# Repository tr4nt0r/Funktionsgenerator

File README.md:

# Funktionsgenerator
Funktionsgenerator basierend auf dem DDS AD9833 mit einem Atmega328PB (Arduino) als Mikrocontroller und einem 1,8" TFT Display

Function generator with AD9833 DDS, Atmega328PB Microcontroller and a 1.8" TFT Display

## Bill of Materials
### AD9833 & µController Board

| Qty | Value | Device | Package | Description | Vendor | Price |
| ---: | :--- | :--- | :--- | :--- | :--- | ---: |
| 1 | | KMR-1.8 SPI ST7735R | | 1.8" TFT Display |  [eBay](https://www.ebay.de/sch/i.html?_from=R40&_trksid=m570.l1313&_nkw=1%2C8%22+tft+spi+st7735r&_sacat=0) | 2,88€ |
| 1 | | SPDT | | Toggle switch for Front Panel Mount | [eBay](https://www.ebay.de/sch/i.html?_from=R40&_trksid=p2380057.m570.l1313.TR12.TRC2.A0.H0.Xtoggle+switch+12mm.TRS0&_nkw=toggle+switch+12mm&_sacat=0) | 3,00€ |
| 1 |  | KY-040 | | Rotary Encoder mit Taster (Ausführung mit Gewinde am Schaft und Befestigungsmutter) |  [eBay](https://www.ebay.de/itm/Drehregler-Drehgeber-Rotary-Encoder-Arduino-KY-040-Potentiometer-Poti-Raspberry/252713917550?hash=item3ad6ec5c6e:g:pIYAAOSwn25aD28N)| 4€ |
| 1 | 1,3k | Resistor | 0603 | | | 0,01€
| 1 | 620 | Resistor | 0603 |||0,01€|
| 8 | 100n | Capacitor | 0603 | | | 0,01€
| 4 | 10k | Resistor | 0603 ||| 0,01€|
| 1 | 10n | Capacitor| 0603||| 0,01€ |
| 1 |16Mhz | Crystal | SMD HC-49/U-S | 16.000MHz QCS HC49/U-S SMD Crystal 16MHz, 20ppm, 2-Pin HC-49/U-S SMD | [RS Components](https://de.rs-online.com/web/p/quarzmodule/8149535/)|0,25€|
| 1 | 1k |Potentiometer|| for Front Panel Mount | [RS Components](https://de.rs-online.com/web/p/products/8427030/)| 5,88€|
| 1 | 25k | Potentiometer || for Front Panel Mount| [RS Components](https://de.rs-online.com/web/p/products/8427059/)| 5,85€|
| 2 | 22p | Capacitor | 0603 | || 0,01€|
| 1 | 24.0Mhz | CFPS-72 | 7 x 5 mm SMD | | [RS Components](https://de.rs-online.com/web/p/products/8141581/)|1,25€|
|1 | 330n | Capacitor | 0603 | || 0,01€|
| 1 | | AD9833BRMZ | MSOP-10 | Programmable Waveform Generator | [Mouser](https://www.mouser.de/ProductDetail/Analog-Devices/AD9833BRMZ?qs=BpaRKvA4VqFt3Bdw9RBKCQ%3D%3D&gclid=Cj0KCQjwjtLZBRDLARIsAKT6fXx8JGdQ5f7k4kLWN22pvajQKU_Hv3pxUgl8WFMx-up7iK0Du9SND08aAm8KEALw_wcB) or [eBay](https://www.ebay.de/sch/i.html?_osacat=0&_odkw=AD9833BRMZ&_from=R40&_trksid=m570.l1313&_nkw=AD9833BRMZ+msop&_sacat=0)|7,79€|
| 1 | | ATMEGA328PB-AU | TQFP-32 | ATMEL - ATMEGA328PB-AU - MCU, 8BIT, ATMEGA, 20MHZ | [RS Components](https://de.rs-online.com/web/p/products/1468920/)|1,61€|
| 1 | 50Ohm | BNC Connector | | for Front Panel Mount | [RS Components](https://de.rs-online.com/web/p/products/5121174/)|2,15€|
| 1 | 10u | EEEFK1C100AR | Panasonic B | Panasonic 10uF 16 Vdc SMD Electrolytic Capacitor | [RS Components](https://de.rs-online.com/web/p/products/0565572/)|0,45€|
| 1 | 47u | Capacitor | Case D| Polarized Tantal Capacitor 10Vdc | [RS Components](https://de.rs-online.com/web/p/products/6993175/) | 0,36€|
| 2 | | LM318D | SO-08 | OpAmp | [RS Components](https://de.rs-online.com/web/p/products/6610524/) | 1,64€|
| 1 | | TLE4270-2D | TO-252 | LDO Voltage Regulator, 850mA, 5 V | [RS Components](https://de.rs-online.com/web/p/ldo-spannungsregler/1109087/) | 2,44€|

### Power Supply Board

| Qty | Value | Device | Package | Description | Vendor | Price |
| ---: | :--- | :--- | :--- | :--- | :--- | ---: |
|2 | 100n| Capacitor | 0603 | ||| 0,01€|
|1 | 2x12V 6VA | Transformer | | PCB Mount | [RS Components](https://de.rs-online.com/web/p/products/1213841/) | 5,75€|
|2 | 100u | EEEFT1C101AR | Panasonic C | Panasonic 100uF 16 Vdc SMD Electrolytic Capacitor | [RS Components](https://de.rs-online.com/web/p/aluminium-elektrolytkondensatoren/7472499/) | 0,35€|
|2 | 1000u/35V | Electrolyic Capacitor |E5-13| | [RS Components](https://de.rs-online.com/web/p/aluminium-elektrolytkondensatoren/7111337/) | 0,46€|
|1 | | MB6S| SOIC-4 | Bridge Rectifier | [RS Components](https://de.rs-online.com/web/p/products/6290322/)|0,35€|
| 1 |+12V| MC7812|DPAK| Positive Voltage Regulator| [RS Components](https://de.rs-online.com/web/p/products/6889250/)|0,70€|
|1|-12V| MC79M12|DPAK | Netgative Voltage Regulator|[RS Components](https://de.rs-online.com/web/p/products/6889326/)|0,65€|

#### Pin Connectors
You will need several pin headers and connectors , 2x2 Pin, 2x3 Pin, 1x 5 Pin. You could use any connector with a pitch of 0,1"/2,54mm either regular pinheaders or [Molex KK 254 Connectors](https://de.rs-online.com/web/c/steckverbinder/leiterplattensteckverbinder/leiterplatten-header/?redirect-relevancy-data=636F3D3126696E3D4931384E53656172636847656E65726963266C753D6465266D6D3D6D61746368616C6C7061727469616C26706D3D5E2E2A2426706F3D31333326736E3D592673723D52656469726563742673743D43415443485F414C4C5F44454641554C542673633D592677633D4E4F4E45267573743D73746966746C6569737465267374613D73746966746C656973746526&r=f&applied-dimensions=4294965668,4293240458,4294519411,4294519436,4294516238,4294878123).

### Images

This work is based on this [howto](https://www.allaboutcircuits.com/projects/how-to-DIY-waveform-generator-analog-devices-ad9833-ATmega328p/) from allaboutcircuits.com

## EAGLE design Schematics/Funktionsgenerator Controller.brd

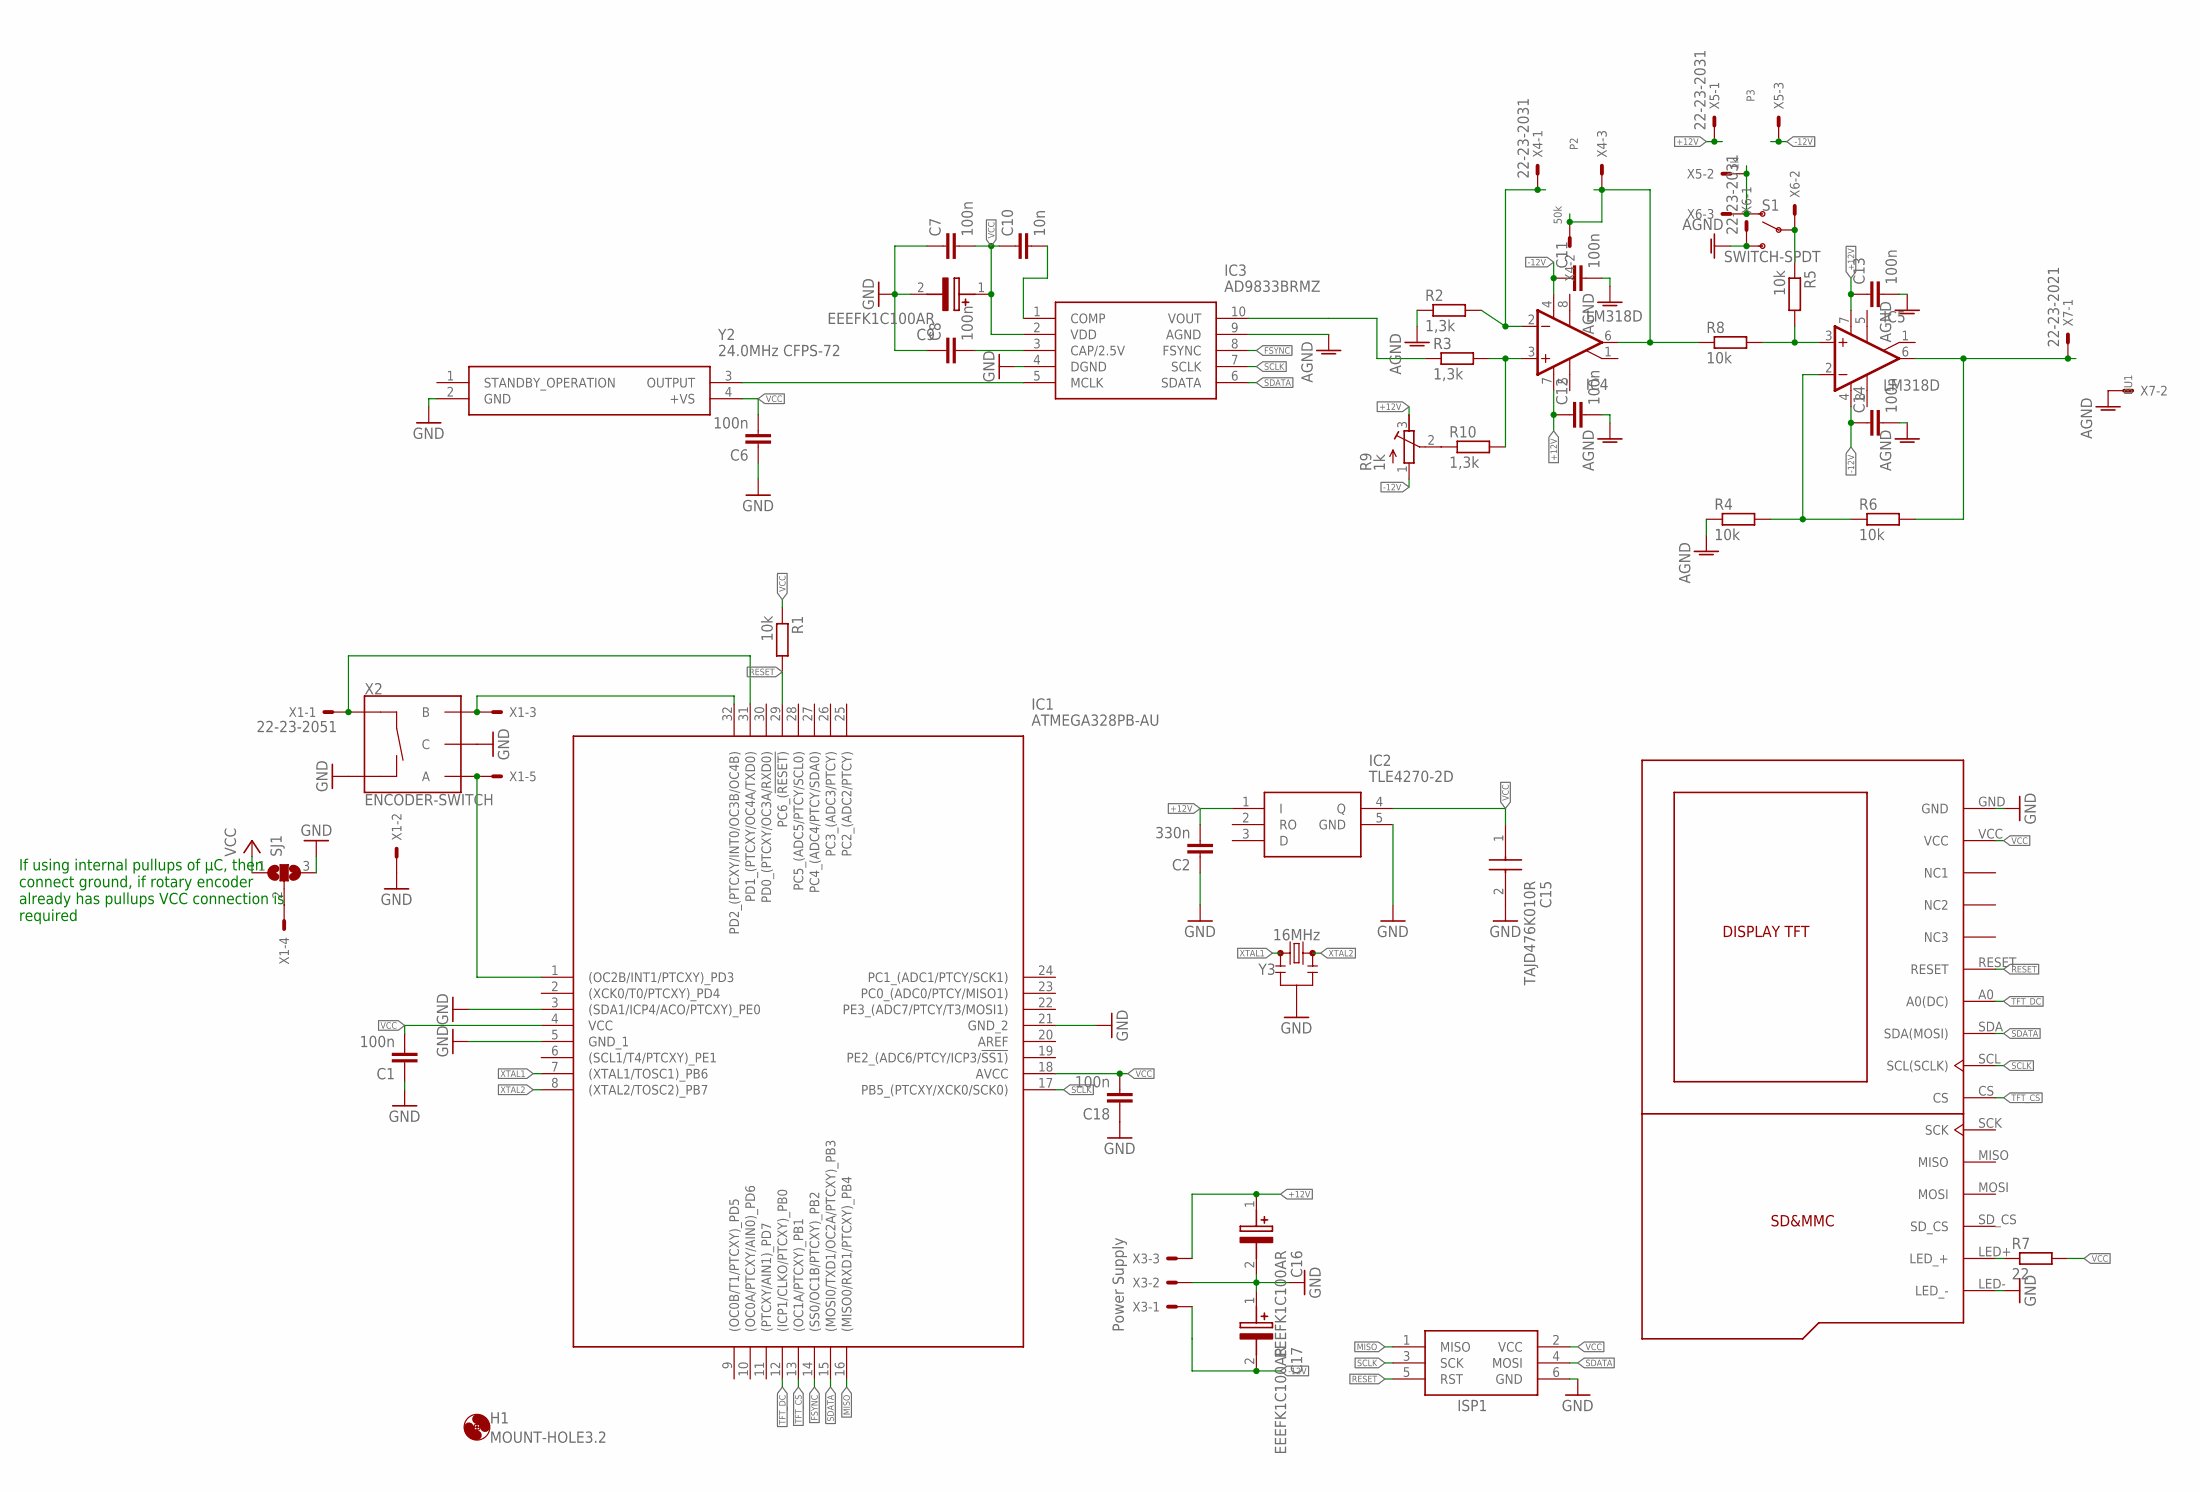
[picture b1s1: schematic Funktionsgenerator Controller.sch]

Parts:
C1, C6, C7, C8, C11, C12, C13, C14, C18: 100n; C0603
C2: 330n; C0603
C9, C16, C17: EEEFK1C100AR; FKV(B)
C10: 10n; C0603
C15: TAJD476K010R; CAPPM7344X310N
H1: MOUNT-HOLE3.2; 3,2
IC1: ATMEGA328PB-AU; QFP80P900X900X120-32N
IC2: TLE4270-2D; PG-TO252-5-11
IC3: AD9833BRMZ; SOP50P490X110-10N
IC4, IC5: LM318D; SO08
ISP1: AVRISP-6; AVRISP
P1: DISPLAY_TFT_1,8; DISPLAY_TFT_1,8-KMR
R1, R4, R5, R6, R8: 10k; R0603
R2, R3, R10: 1,3k; R0603
R7: 22; R0603
R9: 1k; EVM3ESX50B
SJ1: SJ2W; SJ_2
X1: 22-23-2051
X3: Power Supply; 22-23-2031
X4, X5, X6: 22-23-2031
X7: 22-23-2021
Y2: 24.0MHz CFPS-72; CFPS-72
Y3: 16MHz; RESONATOR-SMD-3.2X1.3

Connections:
+12V: C2.2, C12.1, C13.1, C16.1 (+), IC2.1 (I), IC4.7 (V+), IC5.7 (V+), R9.3 (E), X3.3, X5.1
-12V: C11.1, C14.1, C17.2 (-), IC4.4 (V-), IC5.4 (V-), R9.1 (A), X3.1, X5.3
AGND: C11.2, C12.2, C13.2, C14.2, IC3.9 (AGND), R2.1, R4.1, X6.1, X7.2
FSYNC: IC1.14 ((SS0/OC1B/PTCXY)_PB2), IC3.8 (FSYNC)
GND: C1.1, C2.1, C6.1, C7.1, C8.1, C9.2 (-), C15.2 (-), C16.2 (-), C17.1 (+), C18.1, IC1.3 ((SDA1/ICP4/ACO/PTCXY)_PE0), IC1.5 (GND_1), IC1.21 (GND_2), IC2.5 (GND), IC3.4 (DGND), ISP1.6 (GND), P1.GND, P1.LED- (LED_-), SJ1.3, X1.2, X3.2, Y2.2 (GND), Y3.2
MISO: IC1.16 ((MISO0/RXD1/PTCXY)_PB4), ISP1.1 (MISO)
unnamed: IC3.5 (MCLK), Y2.3 (OUTPUT)
unnamed: C8.2, IC3.3 (CAP/2.5V)
unnamed: IC4.3 (+IN), R3.2, R10.2
unnamed: C10.2, IC3.1 (COMP)
unnamed: IC3.10 (VOUT), R3.1
unnamed: IC4.2 (-IN), R2.2, X4.1
unnamed: R5.1, X6.2
unnamed: X5.2, X6.3
unnamed: IC4.6 (OUT), R8.1, X4.2, X4.3
unnamed: IC5.6 (OUT), R6.2, X7.1
unnamed: IC5.2 (-IN), R4.2, R6.1
unnamed: SJ1.2, X1.4
unnamed: IC5.3 (+IN), R5.2, R8.2
unnamed: R9.2 (S), R10.1
unnamed: P1.LED+ (LED_+), R7.1
RESET: IC1.29 (PC6_(!RESET)), ISP1.5 (RST), P1.RESET, R1.2
ROT_A: IC1.1 ((OC2B/INT1/PTCXY)_PD3), X1.5
ROT_B: IC1.32 (PD2_(PTCXY/INT0/OC3B/OC4B)), X1.3
ROT_BTN: IC1.31 (PD1_(PTCXY/OC4A/TXD0)), X1.1
SCLK: IC1.17 (PB5_(PTCXY/XCK0/SCK0)), IC3.7 (SCLK), ISP1.3 (SCK), P1.SCL (SCL(SCLK))
SDATA: IC1.15 ((MOSI0/TXD1/OC2A/PTCXY)_PB3), IC3.6 (SDATA), ISP1.4 (MOSI), P1.SDA (SDA(MOSI))
TFT_CS: IC1.13 ((OC1A/PTCXY)_PB1), P1.CS
TFT_DC: IC1.12 ((ICP1/CLKO/PTCXY)_PB0), P1.A0 (A0(DC))
VCC: C1.2, C6.2, C7.2, C9.1 (+), C10.1, C15.1 (+), C18.2, IC1.4 (VCC), IC1.18 (AVCC), IC2.4 (Q), IC3.2 (VDD), ISP1.2 (VCC), P1.VCC, R1.1, R7.2, SJ1.1, Y2.4 (+VS)
XTAL1: IC1.7 ((XTAL1/TOSC1)_PB6), Y3.1
XTAL2: IC1.8 ((XTAL2/TOSC2)_PB7), Y3.3

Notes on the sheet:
If using internal pullups of µC, then connect ground, if rotary encoder already has pullups VCC connection is required

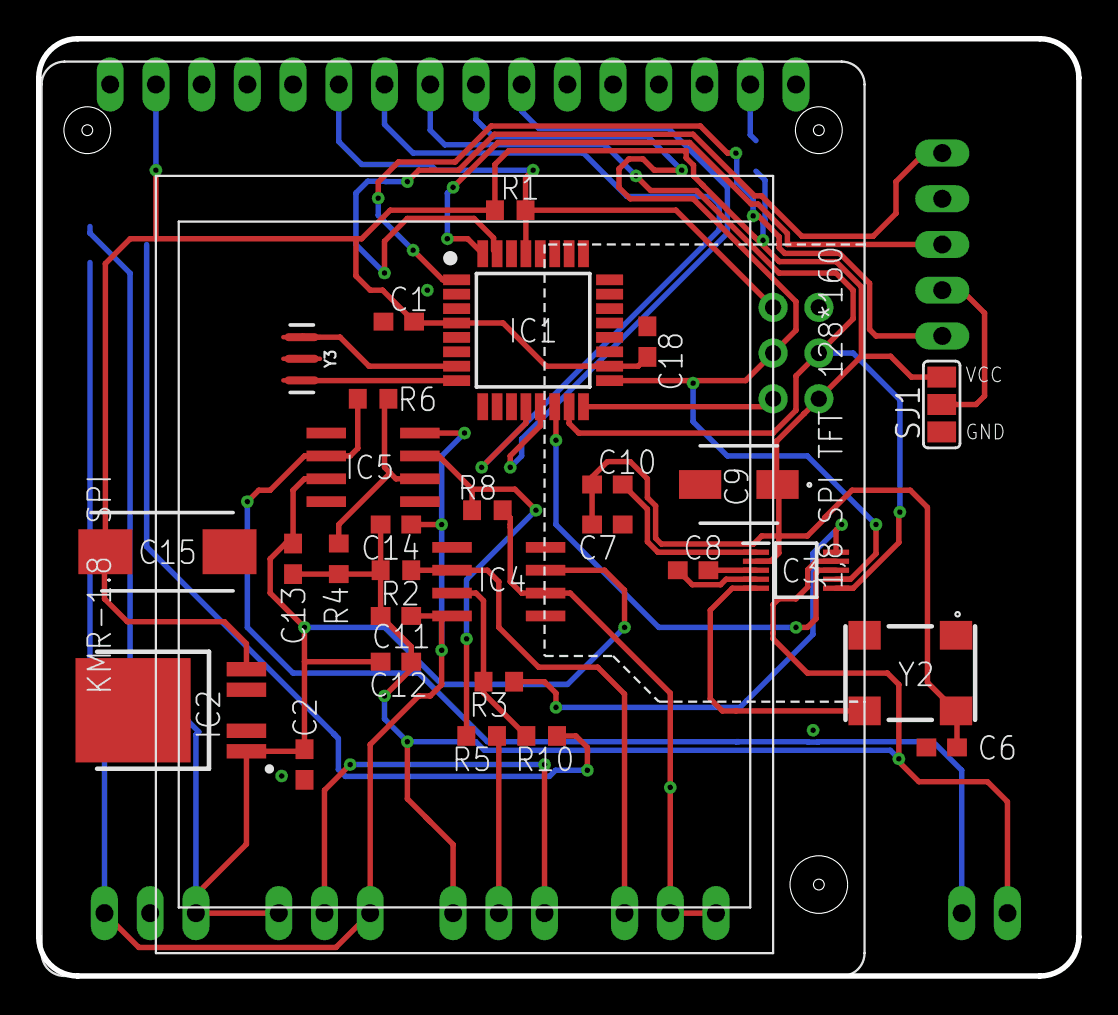
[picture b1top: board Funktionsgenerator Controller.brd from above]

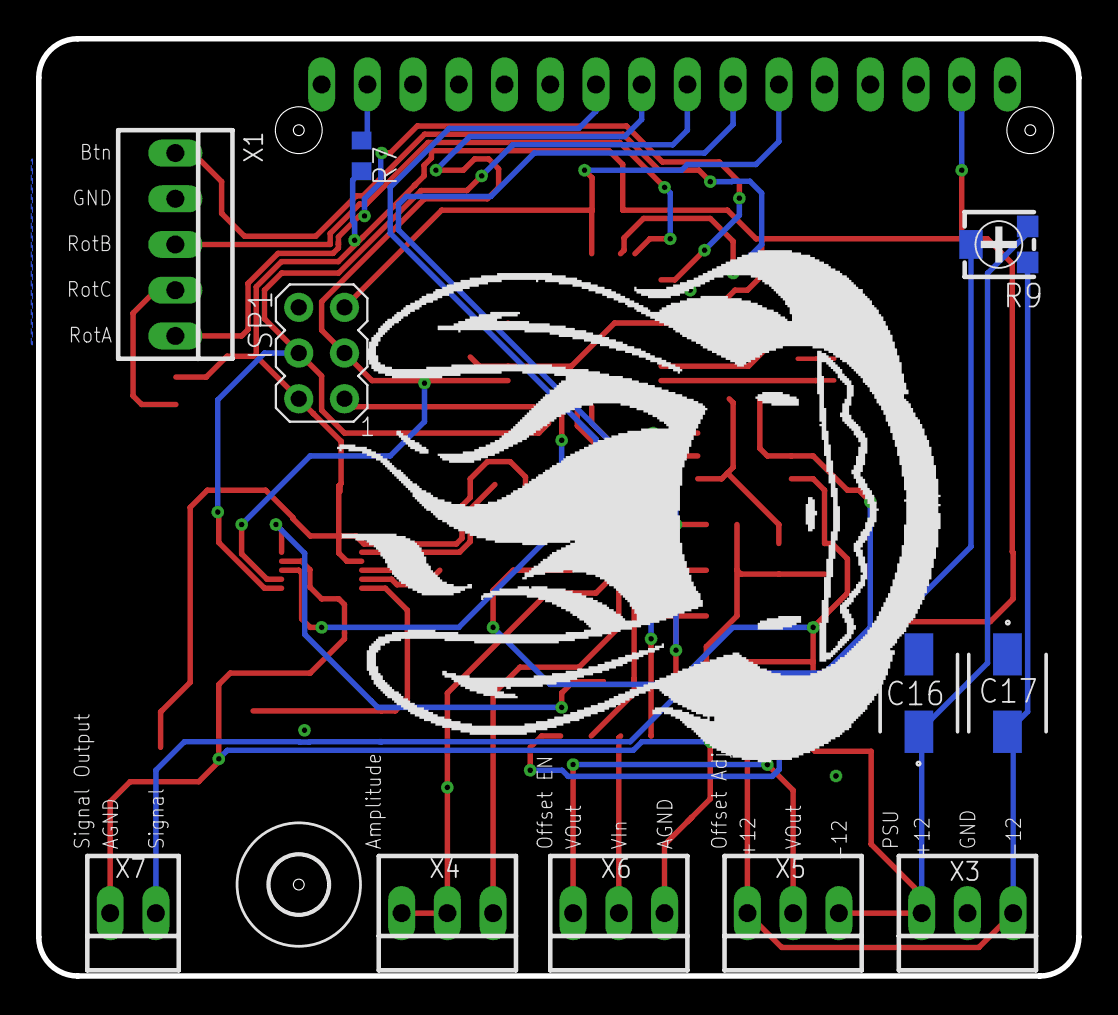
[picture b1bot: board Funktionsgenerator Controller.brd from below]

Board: 2 copper layers, 57.8 x 52.1 mm, 42 parts (12 on the bottom side), 32 nets.

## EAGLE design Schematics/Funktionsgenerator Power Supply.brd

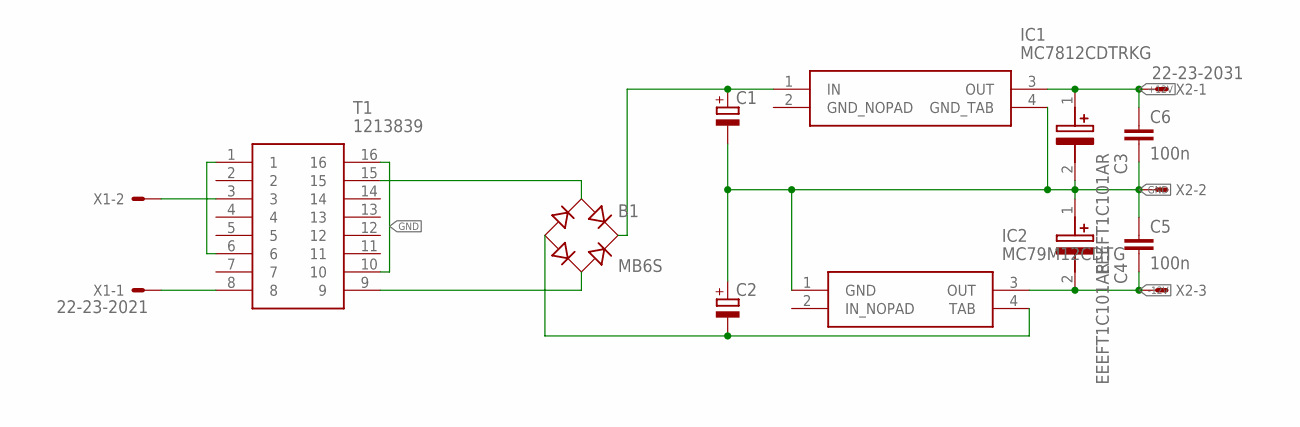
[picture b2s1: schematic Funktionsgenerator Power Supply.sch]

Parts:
B1: MB6S; SOIC-4
C1, C2: CPOL-EUE5-13; E5-13
C3, C4: EEEFT1C101AR; HBV(C)
C5, C6: 100n; C0603
IC1: MC7812CDTRKG; TO229P990X238-4N
IC2: MC79M12CDTG; TO229P990X238-4N
T1: 1213839; DIPS3500W80P500L4400H2300Q16N
X1: 22-23-2021
X2: 22-23-2031

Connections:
+12V: C3.1 (+), C6.1, IC1.3 (OUT), X2.1
-12V: C4.2 (-), C5.2, IC2.3 (OUT), X2.3
GND: C1.-, C2.+, C3.2 (-), C4.1 (+), C5.1, C6.2, IC1.4 (GND_TAB), IC2.1 (GND), T1.10, T1.16, X2.2
GND_NOPAD: IC1.2 (GND_NOPAD)
unnamed: T1.1, T1.6
unnamed: T1.3, X1.2
unnamed: T1.8, X1.1
unnamed: B1.~1 (AC1), T1.15
unnamed: B1.~2 (AC2), T1.9
unnamed: B1.-, C2.-, IC2.4 (TAB)
unnamed: B1.+, C1.+, IC1.1 (IN)

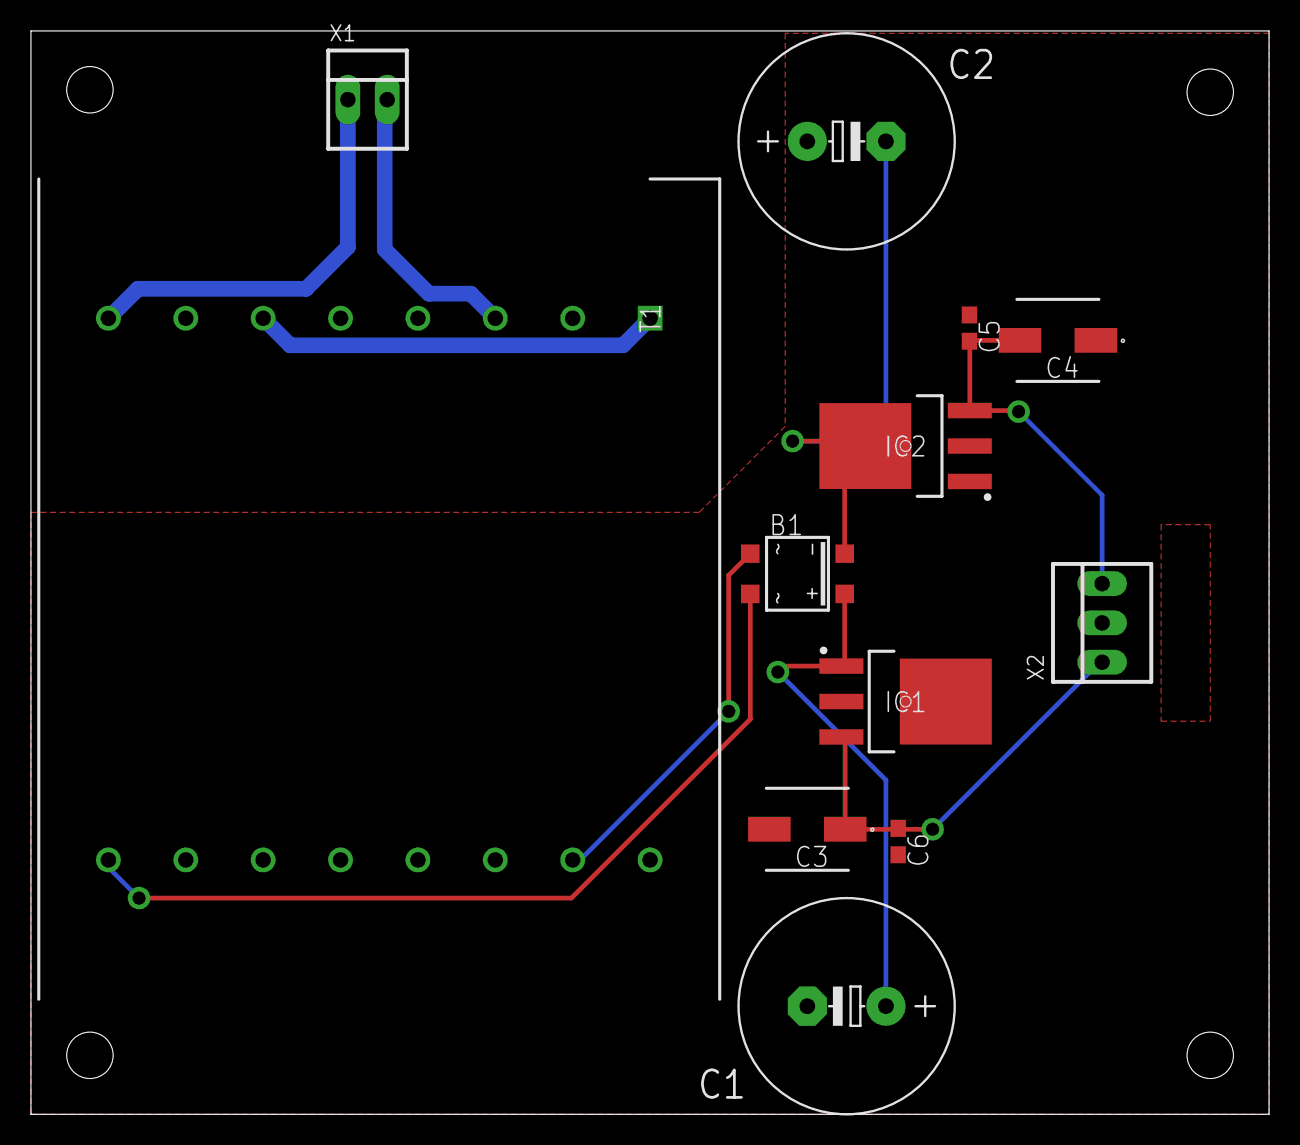
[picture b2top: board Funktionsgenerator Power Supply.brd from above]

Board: 2 copper layers, 80.0 x 70.0 mm, 12 parts (0 on the bottom side), 10 nets.

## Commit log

2018-06-27 Revision 1
    Fertige Platinen für Platinenfräse geeignet.
    Todo: Bauteile Bezeichnungen auf Silkscreen richtig positionieren
2018-06-28 Added BOM
2018-06-28 created todo list
2018-07-02 Moved Files to subfolder
2018-07-02 commit of unmodified firmware
2018-07-02 added VisualMicro stuff to .gitignore
2018-07-02 moved variable definitions to definitions.h using pow method from math.h
2018-07-02 removed unused variable
2018-07-02 .sln added to .gitignore
2018-07-03 changed from LCD to TFT, added Bootup Scrreen
2018-07-05 changed display to ST7735,added Bootupmsg
2018-07-10 Added Resistor to limit current for TFT Backlight
    Das TFT Display wurde zu heiß, da der Vorwiderstand für die Hintergrundbeleuchtung des TFT lediglich 6Ohm beträgt. Durch einen weiteren Vorwiderstand von 22Ohm konnte die Wärmeentwicklung des Display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
2018-07-10 Changes to Bootup Scrreen, some fixes
2018-07-10 Added Vector file for MDF/Acrylic Case
2018-07-11 minor modifications and fixes
2018-07-11 forgot some squares, repositioned text
2018-07-11 Rotary Encoder zu Liste hinzugefügt
2018-07-12 added Encoder Library
2018-07-12 a lot of changes
2018-07-12 VCC on encoder connector for external pull-up
2018-07-13 removed references to LiquidCrystal lib
2018-07-13 added TFT Navigation Menu, libraries added as submodules
2018-07-14 added Menu for waveform selection
2018-07-15 added mainscreen showing frequency, hold button for power on/off
2018-07-16 moved labels on, added net names
2018-07-18 added functionality for changing frequency
2018-07-18 fixed overflow bug in frequency change function
2018-07-19 optimized algorithm for displaying digits
2018-07-20 commented out all deprecated functions
2018-07-23 freqSet Menu
2018-07-25 Create LICENSE
2018-07-25 Freq changing digit by digit, added Menu class to remove enum from global scope
2018-07-26 some cleanup
2018-07-26 renamed Direction Enum
2018-09-27 Added trimmer for offset adjustment and some fixes
2019-02-18 added images

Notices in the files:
parts and their libraries:
SparkFun-Clocks: Licensing: Creative Commons ShareAlike 4.0 International - https://creativecommons.org/licenses/by-sa/4.0
